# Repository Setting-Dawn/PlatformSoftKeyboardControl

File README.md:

#  PlatformSoftKeyboardControl 
Control a 2 Degree of Freedom Platform using a soft sensing sheet.

This README is also used as the main page for the Doxygen-generated documentation.
The remainder of this file contains project details, diagrams, and usage
information.
# PlatformSoftKeyboardControl 

Project Goal:

Control a 2 Degree of Freedom Platform using a custom piezoresistive sensing sheet.
## Mechanical Considerations
The balancing table is controlled by two motors connected to the table's surface via a strut with two ball joints that control rotation about perpendicular axes.

## Software Design
### Task Diagram

### Webserver Task 
The ESP32 hosts its own wifi on which it hosts a webpage on 192.168.5.1 that communicates the recorded data in csv forma to either the user or an external program that interprets it. The functionality of this task is based on an example by .

### Motor Control Task 
The motor control task awaits confirmation that the IMU has initialized and then begins operating the motor PIDs according to the setpoint stored in the xBar and yBar shares.

### Material Reading Task 
In order to perform EIT analysis, a series of voltage differences needs to be measured. For one complete measurement, one electrode is grounded while its neighboring electrode is supplied with a current while the remaining electrodes are used to measure the voltage differences. This is then repeated for each electrode. This task is responsible for taking those individual datapoints and reporting the resulting 208 values to the webpage task to be published in csv format.

### PyEIT interpretation
A python script using the  is able to read the data hosted by the webpage and analyze any changes in resistivity of the material. The resulting centroid is then passed back to the webpage using url arguments.

## Other Code Used
- Liu, et al:
+ - https://github.com/eitcom/pyEIT 
- bryanduxbury:
+ - https://github.com/bryanduxbury/adc128d818_driver 
- yuskegoto:
+ - https://github.com/yuskegoto/PCA9956 
- spluttflob:
+ - PrintStream Library https://github.com/spluttflob/Arduino-PrintStream.git 
+ - ME507 Support Library https://github.com/spluttflob/ME507-Support.git
- madhephaestus:
+ - https://github.com/madhephaestus/ESP32Encoder

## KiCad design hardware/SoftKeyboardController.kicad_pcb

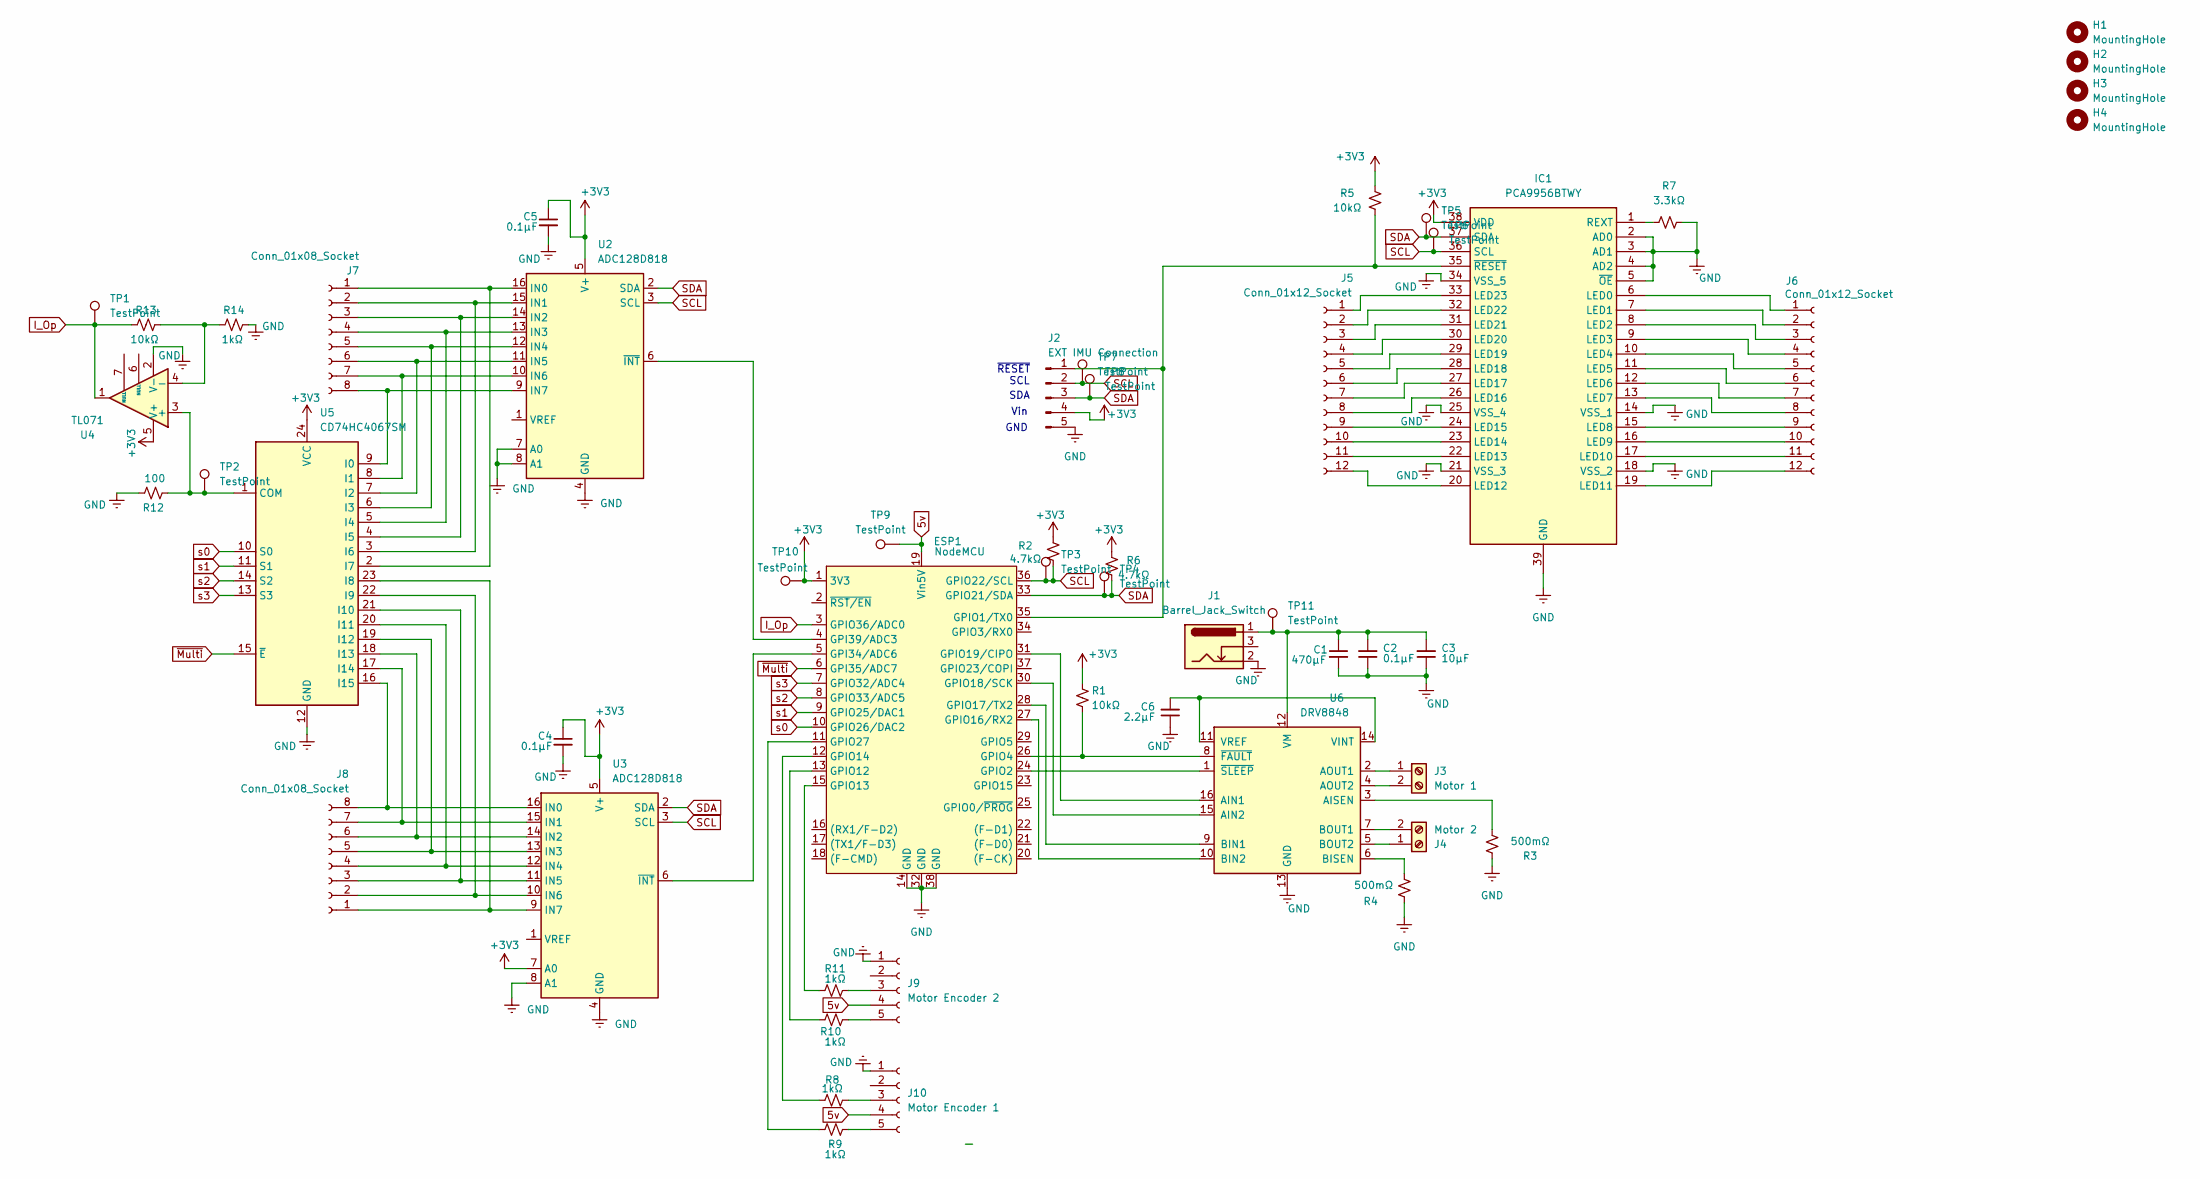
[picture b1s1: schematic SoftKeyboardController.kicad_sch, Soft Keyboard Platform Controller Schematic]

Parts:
C1: 470μF; CP_Radial_D10.0mm_P5.00mm
C2, C4, C5: 0.1μF; C_0805_2012Metric
C3: 10μF; C_0805_2012Metric
C6: 2.2μF; C_0805_2012Metric
ESP1: NodeMCU; ESP32_NodeMCU_KeeYees
H1, H2, H3, H4: MountingHole; MountingHole_2.5mm
IC1: PCA9956BTWY; SOP50P640X110-39N; Manufacturer_Part_Number PCA9956BTWY; Mouser Part Number 771-PCA9956BTWY
J1: Barrel_Jack_Switch; BarrelJack_CUI_PJ-102AH_Horizontal
J2: EXT IMU Connection; PinHeader_1x05_P2.54mm_Vertical
J3: Motor 1; TerminalBlock_Phoenix_MKDS-1,5-2_1x02_P5.00mm_Horizontal
J4: Motor 2; TerminalBlock_Phoenix_MKDS-1,5-2_1x02_P5.00mm_Horizontal
J5, J6: Conn_01x12_Socket; PinSocket_1x12_P2.54mm_Vertical
J7, J8: Conn_01x08_Socket; PinSocket_1x08_P2.54mm_Vertical
J9: Motor Encoder 2; Molex_KK-396_A-41792-0005_1x05_P3.96mm_Horizontal
J10: Motor Encoder 1; Molex_KK-396_A-41792-0005_1x05_P3.96mm_Horizontal
R1, R5, R13: 10kΩ; R_0805_2012Metric
R2, R6: 4.7kΩ; R_0805_2012Metric
R3, R4: 500mΩ; R_0805_2012Metric
R7: 3.3kΩ; R_0805_2012Metric
R8, R9, R10, R11, R14: 1kΩ; R_0805_2012Metric
R12: 100; R_0805_2012Metric
TP1, TP2, TP3, TP4, TP5, TP6, TP7, TP8, TP9, TP10, TP11: TestPoint; TestPoint_Loop_D1.80mm_Drill1.0mm_Beaded
U2, U3: ADC128D818; TSSOP-16_4.4x5mm_P0.65mm
U4: TL071; SOT-23-5
U5: CD74HC4067SM; SSOP-24_5.3x8.2mm_P0.65mm
U6: DRV8848; TSSOP-16-1EP_4.4x5mm_P0.65mm

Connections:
5v: ESP1.19 (Vin5V), J9.4, J10.4, TP9.1
+3V3: C4.1, C5.1, ESP1.1 (3V3), IC1.38 (VDD), J2.4, R1.1, R2.1, R5.1, R6.1, TP10.1, U2.5 (V+), U3.5 (V+), U3.7 (A0), U4.5 (V+), U5.24 (VCC)
GND: C1.2, C2.1, C3.1, C4.2, C5.2, C6.1, ESP1.14 (GND), ESP1.32 (GND), ESP1.38 (GND), IC1.2 (AD0), IC1.3 (AD1), IC1.4 (AD2), IC1.5 (~OE), IC1.14 (VSS_1), IC1.18 (VSS_2), IC1.21 (VSS_3), IC1.25 (VSS_4), IC1.34 (VSS_5), IC1.39 (GND), J1.2, J2.5, J9.1, J10.1, R3.1, R4.1, R7.1, R12.1, R14.1, U2.4 (GND), U2.7 (A0), U2.8 (A1), U3.4 (GND), U3.8 (A1), U4.2 (V-), U5.12 (GND), U6.13 (GND), U6.17 (GND)
I_Op: ESP1.3 (GPIO36/ADC0), R13.2, TP1.1, U4.1
unnamed: ESP1.5 (GPI34/ADC6), U3.6 (~INT)
unnamed: ESP1.4 (GPI39/ADC3), U2.6 (~INT)
unnamed: ESP1.35 (GPIO1/TX0), IC1.35 (~RESET), J2.1, R5.2
unnamed: ESP1.24 (GPIO2), U6.1 (~SLEEP)
unnamed: ESP1.26 (GPIO4), R1.2, U6.8 (~FAULT)
unnamed: ESP1.13 (GPIO12), R10.1
unnamed: ESP1.15 (GPIO13), R11.1
unnamed: ESP1.12 (GPIO14), R8.1
unnamed: ESP1.27 (GPIO16/RX2), U6.10 (BIN2)
unnamed: ESP1.28 (GPIO17/TX2), U6.9 (BIN1)
unnamed: ESP1.30 (GPIO18/SCK), U6.15 (AIN2)
unnamed: ESP1.31 (GPIO19/CIPO), U6.16 (AIN1)
unnamed: ESP1.11 (GPIO27), R9.1
unnamed: IC1.6 (LED0), J6.1
unnamed: IC1.7 (LED1), J6.2
unnamed: IC1.8 (LED2), J6.3
unnamed: IC1.9 (LED3), J6.4
unnamed: IC1.10 (LED4), J6.5
unnamed: IC1.11 (LED5), J6.6
unnamed: IC1.12 (LED6), J6.7
unnamed: IC1.13 (LED7), J6.8
unnamed: IC1.15 (LED8), J6.9
unnamed: IC1.16 (LED9), J6.10
unnamed: IC1.17 (LED10), J6.11
unnamed: IC1.19 (LED11), J6.12
unnamed: IC1.20 (LED12), J5.12
unnamed: IC1.22 (LED13), J5.11
unnamed: IC1.23 (LED14), J5.10
unnamed: IC1.24 (LED15), J5.9
unnamed: IC1.26 (LED16), J5.8
unnamed: IC1.27 (LED17), J5.7
unnamed: IC1.28 (LED18), J5.6
unnamed: IC1.29 (LED19), J5.5
unnamed: IC1.30 (LED20), J5.4
unnamed: IC1.31 (LED21), J5.3
unnamed: IC1.32 (LED22), J5.2
unnamed: IC1.33 (LED23), J5.1
unnamed: IC1.1 (REXT), R7.2
unnamed: J3.1, U6.2 (AOUT1)
unnamed: J3.2, U6.4 (AOUT2)
unnamed: J4.1, U6.5 (BOUT2)
unnamed: J4.2, U6.7 (BOUT1)
unnamed: J7.1, U2.16 (IN0), U5.2 (I7)
unnamed: J7.2, U2.15 (IN1), U5.3 (I6)
unnamed: J7.3, U2.14 (IN2), U5.4 (I5)
unnamed: J7.4, U2.13 (IN3), U5.5 (I4)
unnamed: J7.5, U2.12 (IN4), U5.6 (I3)
unnamed: J7.6, U2.11 (IN5), U5.7 (I2)
unnamed: J7.7, U2.10 (IN6), U5.8 (I1)
unnamed: J7.8, U2.9 (IN7), U5.9 (I0)
unnamed: J8.1, U3.9 (IN7), U5.23 (I8)
unnamed: J8.2, U3.10 (IN6), U5.22 (I9)
unnamed: J8.3, U3.11 (IN5), U5.21 (I10)
unnamed: J8.4, U3.12 (IN4), U5.20 (I11)
unnamed: J8.5, U3.13 (IN3), U5.19 (I12)
unnamed: J8.6, U3.14 (IN2), U5.18 (I13)
unnamed: J8.7, U3.15 (IN1), U5.17 (I14)
unnamed: J8.8, U3.16 (IN0), U5.16 (I15)
unnamed: J9.3, R11.2
unnamed: J9.5, R10.2
unnamed: J10.3, R8.2
unnamed: J10.5, R9.2
unnamed: R12.2, TP2.1, U4.3 (+), U5.1 (COM)
unnamed: R13.1, R14.2, U4.4 (-)
unnamed: R3.2, U6.3 (AISEN)
unnamed: R4.2, U6.6 (BISEN)
unnamed: C6.2, U6.11 (VREF), U6.14 (VINT)
unnamed: C1.1, C2.2, C3.2, J1.1, TP11.1, U6.12 (VM)
SCL: ESP1.36 (GPIO22/SCL), IC1.36 (SCL), J2.2, R2.2, TP3.1, TP6.1, TP7.1, U2.3 (SCL), U3.3 (SCL)
SDA: ESP1.33 (GPIO21/SDA), IC1.37 (SDA), J2.3, R6.2, TP4.1, TP5.1, TP8.1, U2.2 (SDA), U3.2 (SDA)
s0: ESP1.10 (GPIO26/DAC2), U5.10 (S0)
s1: ESP1.9 (GPIO25/DAC1), U5.11 (S1)
s2: ESP1.8 (GPIO33/ADC5), U5.14 (S2)
s3: ESP1.7 (GPIO32/ADC4), U5.13 (S3)
~Multi: ESP1.6 (GPI35/ADC7), U5.15 (~E)

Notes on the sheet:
GND
~{RESET}
Vin
SDA
SCL

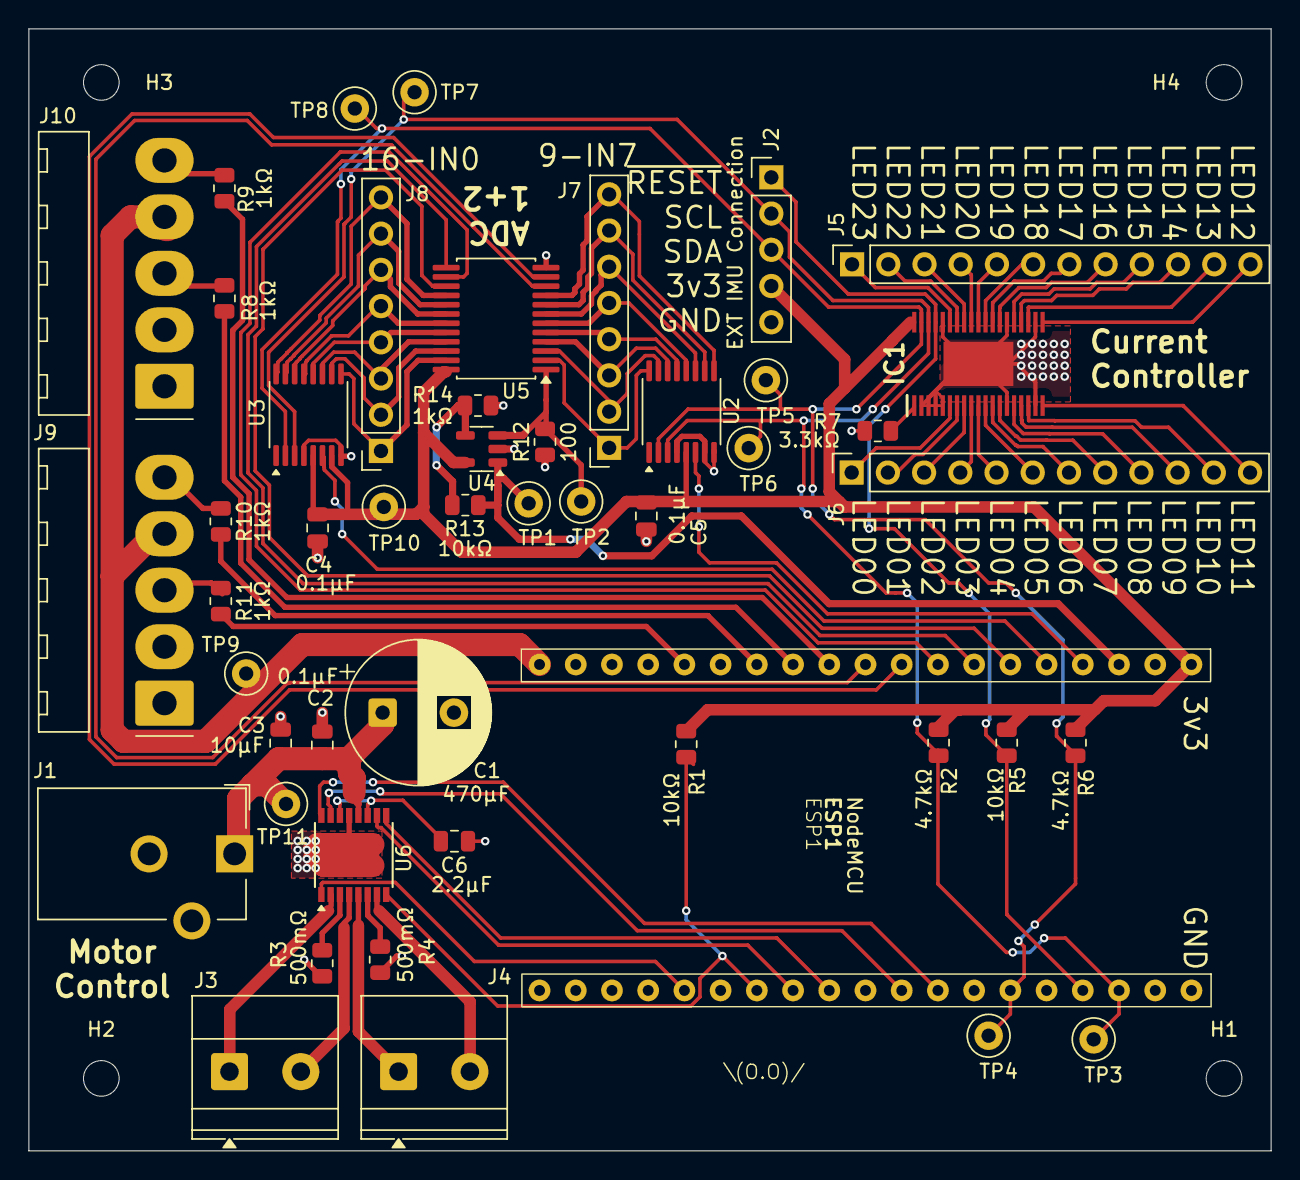
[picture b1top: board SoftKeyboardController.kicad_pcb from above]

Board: 2 copper layers, 87.1 x 78.7 mm, 52 parts (0 on the bottom side), 79 nets.

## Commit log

2025-10-10 10/9 Lab update
    10/9 Lab
2025-10-16 init
2025-10-17 v1.0 Schematic
2025-10-17 Adjusted Schematic to v1.1
2025-10-17 Update Schematic to v1.1 (redo of pull request)
2025-10-24 ADC chips
2025-10-24 Added Transistors & ADCs to schematic. V1 of PCB
2025-10-24 Delete SoftKeyboardController/temp.kicad_sch
    Removed temp files created during backup recovery
2025-10-30 Shrink Footprint
    Relocated and re-traced board to improve overall footprint
2025-10-30 Added motor encoder connections
2025-11-07 Started code
    Created motor class and some function definitions
2025-11-07 Remapped Board again
    Version of Board before ordering
2025-11-08 changed capacitor footprint to reflect actual capacitor
2025-11-09 re ran gerber file export
2025-11-09 updated zip file with gerber files
2025-11-13 remove errored lock file
2025-11-14 rename hardware folder for clarity
2025-11-14 get rid of session lock file accidentally uploaded
2025-11-17 initial setup for material reading
2025-11-21 Added Skeleton for Basic Control Loop
2025-11-21 created base communication task
2025-12-01 Create script to communicate with pyEIT in python
    Also includes fake voltage values to test pyEIT solver code
2025-12-02 Restructured and Added IMU class
2025-12-03 Update motor control class
2025-12-04 Rewrite functions to limit requests sent to the esp webpage
2025-12-04 added queues and shares for communication
2025-12-04 fix missing commit
2025-12-05 IMUReader Added to Main
    IMUReader Added to Main
2025-12-05 IMUReader Changes
    Created separate .cpp, .h files for the IMU Reader function
2025-12-05 Control Law Algorithm
    Please work
2025-12-05 Complete Motor Controller platform.io project
2025-12-05 Balancing Robot Code
2025-12-05 add cycling measurements
2025-12-05 changed current controller address to match default
2025-12-05 adjusted shares
2025-12-09 Final Version of Code
    Compiled motor control code with material reading code
2025-12-09 Rearranged File structure
2025-12-09 small change to board reflecting fixed SCL and SDA miswiring
2025-12-10 Add doxygen files
2025-12-10 add license
2025-12-10 Expanded README
    Expanded README
2025-12-10 update doxygen
2025-12-10 fix README not implementing as doxygen mainpage
2025-12-10 Revise README.md main page header
2025-12-10 attempt to fix broken doxy links
2025-12-11 please be fixed this time
2025-12-11 again?
2025-12-11 trying again
2025-12-11 again3
2025-12-11 again4
2025-12-11 again5
2025-12-11 clear doxygen files
2025-12-11 re-add doxygen files
2025-12-11 again6
2025-12-11 it was a capitalization issue
2025-12-11 it works! attach README correctly in doxygen
2025-12-11 Added space in README to fix pages updating
